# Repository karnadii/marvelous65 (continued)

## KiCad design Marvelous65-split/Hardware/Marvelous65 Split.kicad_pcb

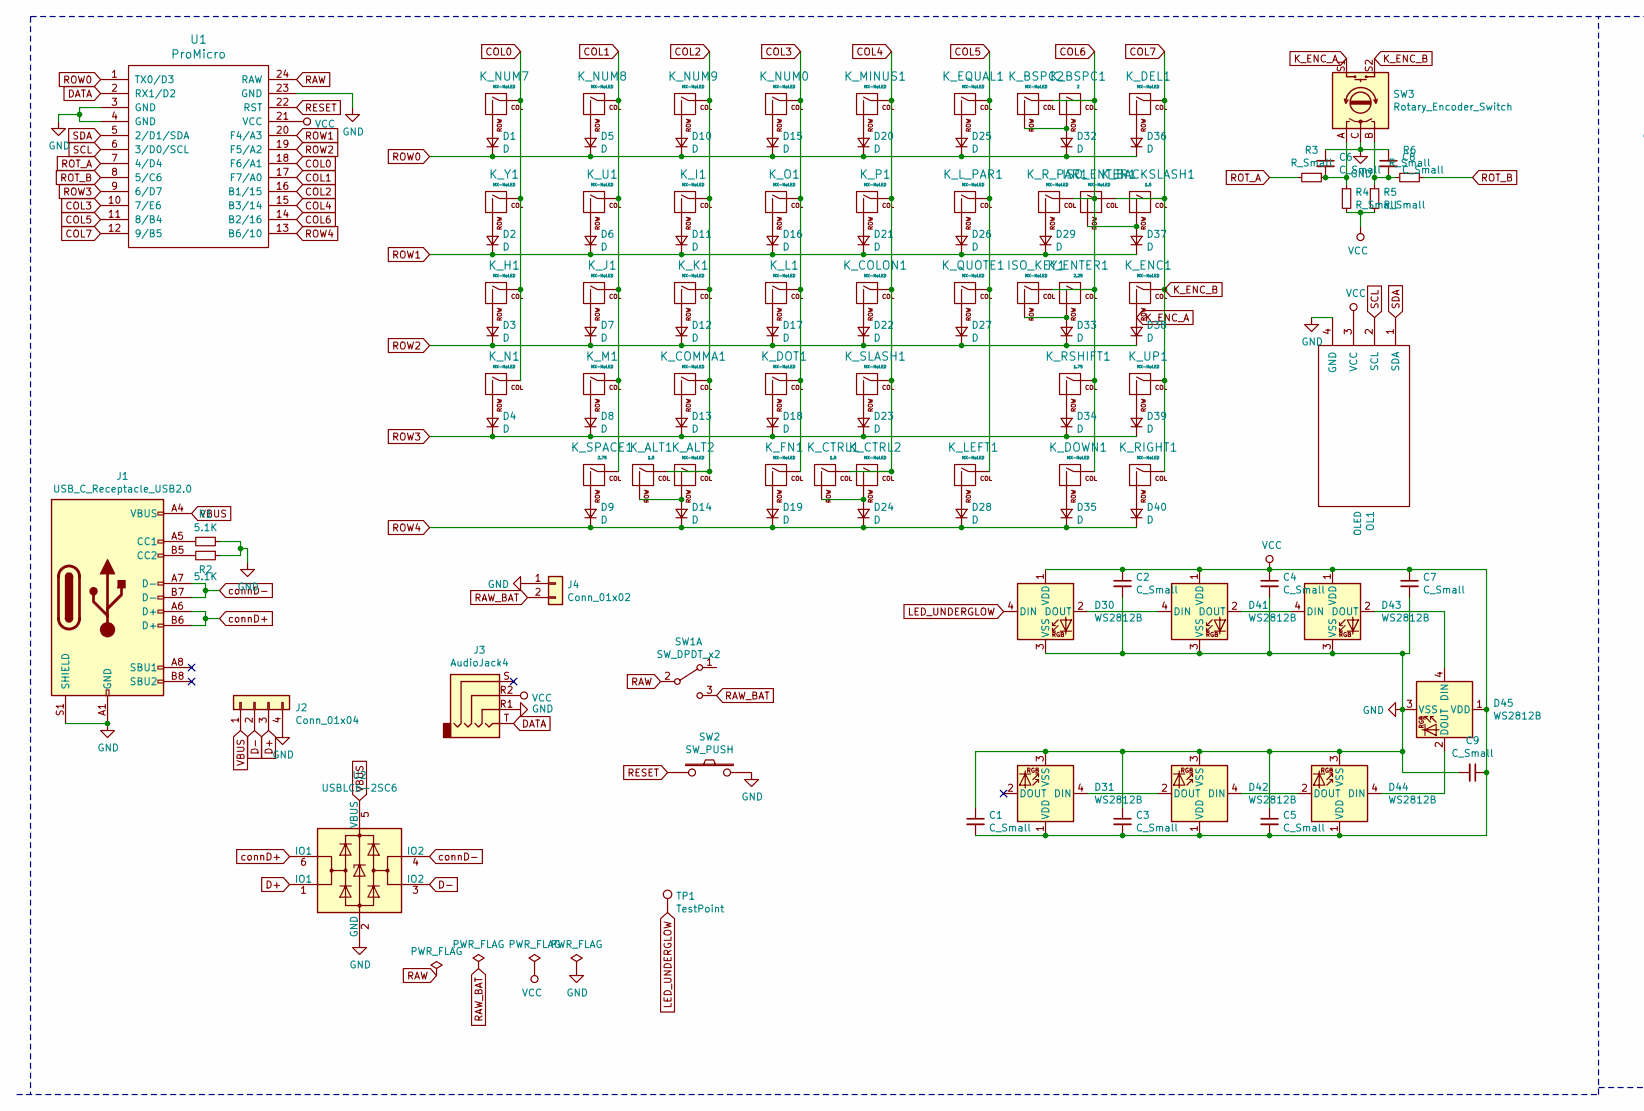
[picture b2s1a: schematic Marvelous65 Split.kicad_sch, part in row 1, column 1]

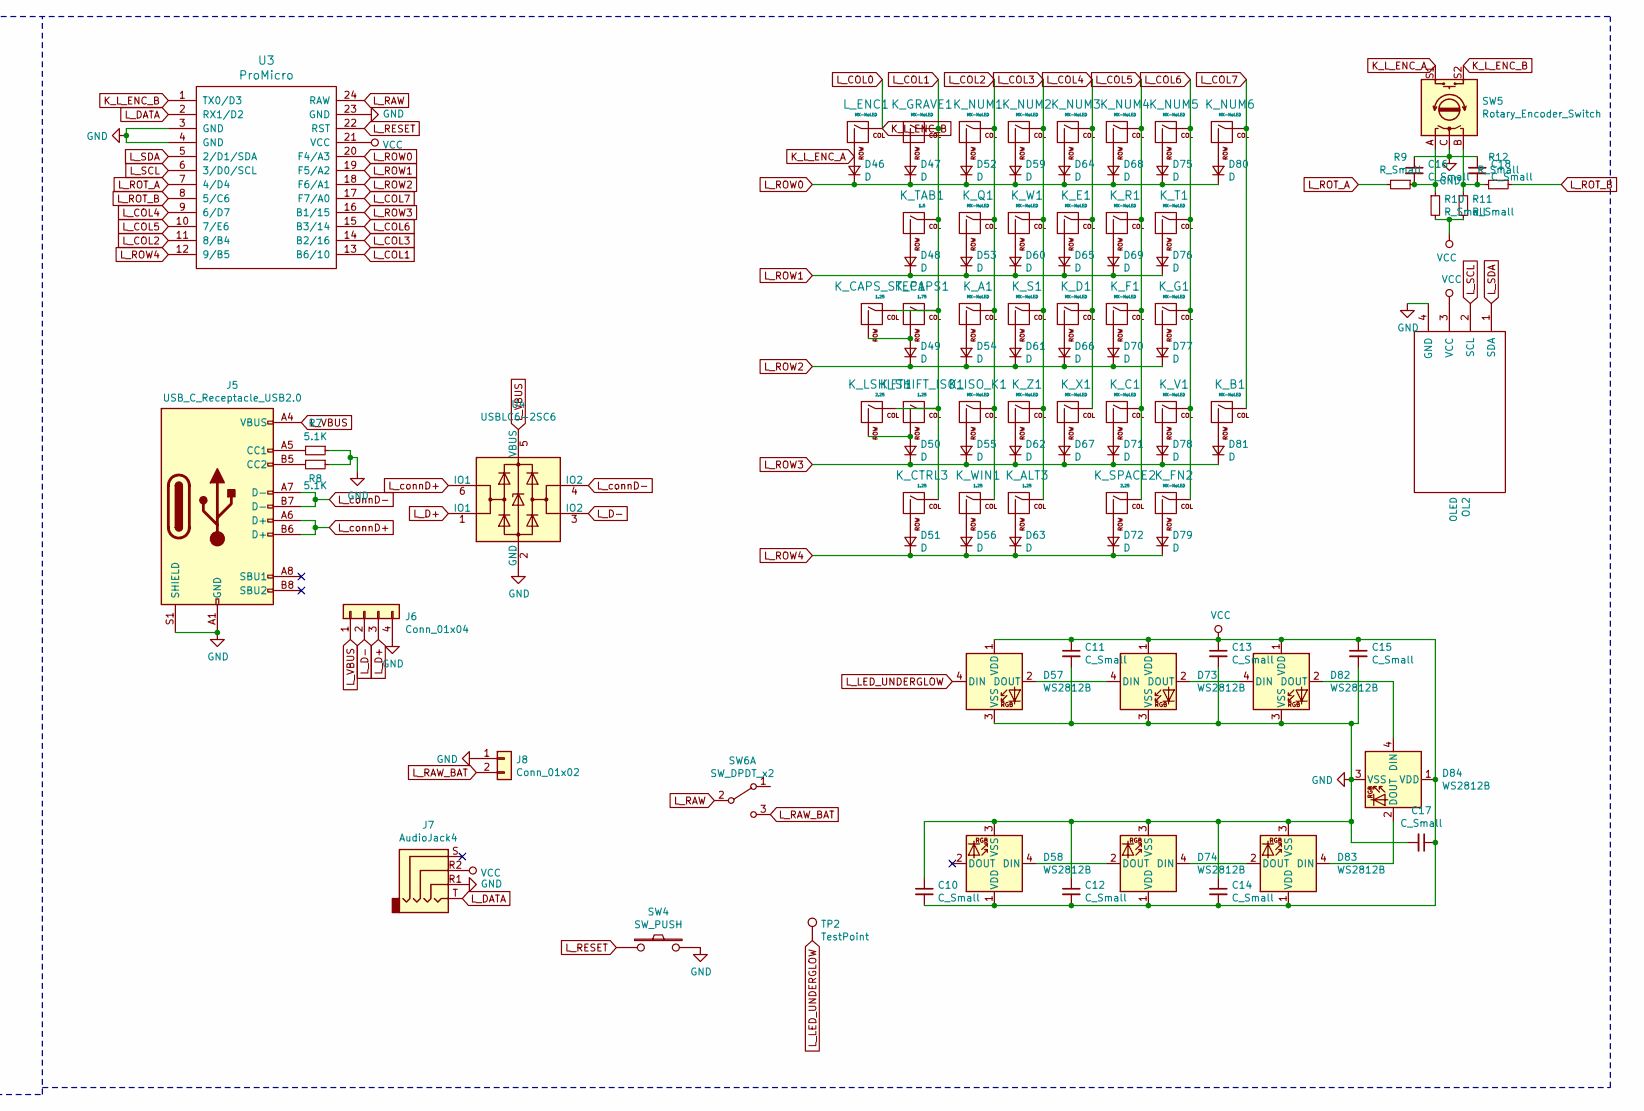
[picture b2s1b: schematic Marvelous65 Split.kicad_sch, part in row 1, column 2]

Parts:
C1, C2, C3, C4, C5, C6, C7, C8, C9, C10, C11, C12, C13, C14, C15, C16, C17, C18: C_Small; C_0805_2012Metric_Pad1.15x1.40mm_HandSolder
D1, D2, D3, D4, D5, D6, D7, D8, D9, D10, D11, D12, D13, D14, D15, D16, D17, D18, D19, D20, D21, D22, D23, D24, D25, D26, D27, D28, D29, D32, D33, D34, D35, D36, D37, D38, D39, D40, D46, D47, D48, D49, D50, D51, D52, D53, D54, D55, D56, D59, D60, D61, D62, D63, D64, D65, D66, D67, D68, D69, D70, D71, D72, D75, D76, D77, D78, D79, D80, D81: D; D_SOD-123
D30, D31, D41, D42, D43, D44, D45, D57, D58, D73, D74, D82, D83, D84: WS2812B; LED_WS2812B_PLCC4_5.0x5.0mm_P3.2mm
ISO_ENTER1: MX-NoLED; MXOnly-ISO-ROTATED-ReversedStabilizers-NoLED
ISO_KEY1: MX-NoLED; MXOnly-1U-NoLED
J1, J5: USB_C_Receptacle_USB2.0; USB_C_Receptacle_HRO_TYPE-C-31-M-12
J2, J6: Conn_01x04; PinSocket_1x04_P2.54mm_Vertical
J3, J7: AudioJack4; Jack_3.5mm_PJ320D_Horizontal
J4, J8: Conn_01x02; JST_XH_S2B-XH-A_1x02_P2.50mm_Horizontal
K_A1: MX-NoLED; MXOnly-1U-NoLED
K_ALT1: 1.5; MXOnly-1.5U-NoLED
K_ALT2: MX-NoLED; MXOnly-1U-NoLED
K_ALT3: 1.25; MXOnly-1.25U-NoLED
K_B1: MX-NoLED; MXOnly-1U-NoLED
K_BACKSLASH1: 1.5; MXOnly-1.5U-NoLED
K_BSPC1: 2; MXOnly-2U-NoLED
K_BSPC2: MX-NoLED; MXOnly-1U-NoLED
K_C1: MX-NoLED; MXOnly-1U-NoLED
K_CAPS1: 1.75; MXOnly-1.75U-NoLED
K_CAPS_STEP1: 1.25; MXOnly-1.25U-NoLED
K_COLON1: MX-NoLED; MXOnly-1U-NoLED
K_COMMA1: MX-NoLED; MXOnly-1U-NoLED
K_CTRL1: 1.5; MXOnly-1.5U-NoLED
K_CTRL2: MX-NoLED; MXOnly-1U-NoLED
K_CTRL3: 1.25; MXOnly-1.25U-NoLED
K_D1: MX-NoLED; MXOnly-1U-NoLED
K_DEL1: MX-NoLED; MXOnly-1U-NoLED
K_DOT1: MX-NoLED; MXOnly-1U-NoLED
K_DOWN1: MX-NoLED; MXOnly-1U-NoLED
K_E1: MX-NoLED; MXOnly-1U-NoLED
K_ENC1: MX-NoLED; MXOnly-1U-NoLED
K_ENTER1: 2.25; MXOnly-2.25U-NoLED
K_EQUAL1: MX-NoLED; MXOnly-1U-NoLED
K_F1: MX-NoLED; MXOnly-1U-NoLED
K_FN1: MX-NoLED; MXOnly-1U-NoLED
K_FN2: MX-NoLED; MXOnly-1.25U-NoLED
K_G1: MX-NoLED; MXOnly-1U-NoLED
K_GRAVE1: MX-NoLED; MXOnly-1U-NoLED
K_H1: MX-NoLED; MXOnly-1U-NoLED
K_I1: MX-NoLED; MXOnly-1U-NoLED
K_ISO_K1: MX-NoLED; MXOnly-1U-NoLED
K_J1: MX-NoLED; MXOnly-1U-NoLED
K_K1: MX-NoLED; MXOnly-1U-NoLED
K_L1: MX-NoLED; MXOnly-1U-NoLED
K_LEFT1: MX-NoLED; MXOnly-1U-NoLED
K_LSHIFT1: 2.25; MXOnly-2.25U-NoLED
K_L_PAR1: MX-NoLED; MXOnly-1U-NoLED
K_M1: MX-NoLED; MXOnly-1U-NoLED
K_MINUS1: MX-NoLED; MXOnly-1U-NoLED
K_N1: MX-NoLED; MXOnly-1U-NoLED
K_NUM0, K_NUM1, K_NUM2, K_NUM3, K_NUM4, K_NUM5, K_NUM6, K_NUM7, K_NUM8, K_NUM9: MX-NoLED; MXOnly-1U-NoLED
K_O1: MX-NoLED; MXOnly-1U-NoLED
K_P1: MX-NoLED; MXOnly-1U-NoLED
K_Q1: MX-NoLED; MXOnly-1U-NoLED
K_QUOTE1: MX-NoLED; MXOnly-1U-NoLED
K_R1: MX-NoLED; MXOnly-1U-NoLED
K_RIGHT1: MX-NoLED; MXOnly-1U-NoLED
K_RSHIFT1: 1.75; MXOnly-1.75U-NoLED
K_R_PAR1: MX-NoLED; MXOnly-1U-NoLED
K_S1: MX-NoLED; MXOnly-1U-NoLED
K_SHIFT_ISO1: 1.25; MXOnly-1.25U-NoLED
K_SLASH1: MX-NoLED; MXOnly-1U-NoLED
K_SPACE1: 2.75; MXOnly-2.75U-ReversedStabilizers-NoLED
K_SPACE2: 2.25; MXOnly-2.25U-ReversedStabilizers-NoLED
K_T1: MX-NoLED; MXOnly-1U-NoLED
K_TAB1: 1.5; MXOnly-1.5U-NoLED
K_U1: MX-NoLED; MXOnly-1U-NoLED
K_UP1: MX-NoLED; MXOnly-1U-NoLED
K_V1: MX-NoLED; MXOnly-1U-NoLED
K_W1: MX-NoLED; MXOnly-1U-NoLED
K_WIN1: 1.25; MXOnly-1.25U-NoLED
K_X1: MX-NoLED; MXOnly-1U-NoLED
K_Y1: MX-NoLED; MXOnly-1U-NoLED
K_Z1: MX-NoLED; MXOnly-1U-NoLED
L_ENC1: MX-NoLED; MXOnly-1U-NoLED
OL1, OL2: OLED
R1, R2, R7, R8: 5.1K; R_0603_1608Metric_Pad1.05x0.95mm_HandSolder
R3, R4, R5, R6, R9, R10, R11, R12: R_Small; R_0603_1608Metric_Pad1.05x0.95mm_HandSolder
SW1, SW6: SW_DPDT_x2; SW_SPDT_PCM12
SW2, SW4: SW_PUSH; SW_SPST_TL3342
SW3, SW5: Rotary_Encoder_Switch; RotaryEncoder_Alps_EC11E-Switch_Vertical_H20mm
TP1, TP2: TestPoint; TestPoint_THTPad_D2.5mm_Drill1.2mm
U1, U3: ProMicro; ProMicro_v3
U2, U4: USBLC6-2SC6; SOT-23-6

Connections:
COL0: K_H1.1 (COL), K_N1.1 (COL), K_NUM7.1 (COL), K_Y1.1 (COL), U1.18 (F6/A1)
COL1: K_J1.1 (COL), K_M1.1 (COL), K_NUM8.1 (COL), K_SPACE1.1 (COL), K_U1.1 (COL), U1.17 (F7/A0)
COL2: K_ALT1.1 (COL), K_ALT2.1 (COL), K_COMMA1.1 (COL), K_I1.1 (COL), K_K1.1 (COL), K_NUM9.1 (COL), U1.16 (B1/15)
COL3: K_DOT1.1 (COL), K_FN1.1 (COL), K_L1.1 (COL), K_NUM0.1 (COL), K_O1.1 (COL), U1.10 (7/E6)
COL4: K_COLON1.1 (COL), K_CTRL1.1 (COL), K_CTRL2.1 (COL), K_MINUS1.1 (COL), K_P1.1 (COL), K_SLASH1.1 (COL), U1.15 (B3/14)
COL5: K_EQUAL1.1 (COL), K_LEFT1.1 (COL), K_L_PAR1.1 (COL), K_QUOTE1.1 (COL), U1.11 (8/B4)
COL6: ISO_KEY1.1 (COL), K_BSPC1.1 (COL), K_BSPC2.1 (COL), K_DOWN1.1 (COL), K_ENTER1.1 (COL), K_RSHIFT1.1 (COL), K_R_PAR1.1 (COL), U1.14 (B2/16)
COL7: ISO_ENTER1.1 (COL), K_BACKSLASH1.1 (COL), K_DEL1.1 (COL), K_ENC1.1 (COL), K_RIGHT1.1 (COL), K_UP1.1 (COL), SW3.S2, U1.12 (9/B5)
D+: J2.3, U2.1 (IO1)
D-: J2.2, U2.3 (IO2)
DATA: J3.T, U1.2 (RX1/D2)
GND: C1.1, C2.2, C3.1, C4.2, C5.1, C6.1, C7.2, C8.1, C9.2, C10.1, C11.2, C12.1, C13.2, C14.1, C15.2, C16.1, C17.2, C18.1, D30.3 (VSS), D31.3 (VSS), D41.3 (VSS), D42.3 (VSS), D43.3 (VSS), D44.3 (VSS), D45.3 (VSS), D57.3 (VSS), D58.3 (VSS), D73.3 (VSS), D74.3 (VSS), D82.3 (VSS), D83.3 (VSS), D84.3 (VSS), J1.A1 (GND), J1.A12 (GND), J1.B1 (GND), J1.B12 (GND), J1.S1 (SHIELD), J2.4, J3.R1, J4.1, J5.A1 (GND), J5.A12 (GND), J5.B1 (GND), J5.B12 (GND), J5.S1 (SHIELD), J6.4, J7.R1, J8.1, OL1.4 (GND), OL2.4 (GND), R1.1, R2.1, R7.1, R8.1, SW2.2, SW3.C, SW4.2, SW5.C, U1.3 (GND), U1.4 (GND), U1.23 (GND), U2.2 (GND), U3.3 (GND), U3.4 (GND), U3.23 (GND), U4.2 (GND)
K_ENC_A: D38.2 (A), K_ENC1.2 (ROW), SW3.S1
K_L_ENC_A: D46.2 (A), L_ENC1.2 (ROW), SW5.S1
K_L_ENC_B: L_ENC1.1 (COL), SW5.S2, U3.1 (TX0/D3)
LED_UNDERGLOW: D30.4 (DIN), TP1.1
L_COL1: K_CAPS1.1 (COL), K_CAPS_STEP1.1 (COL), K_CTRL3.1 (COL), K_GRAVE1.1 (COL), K_LSHIFT1.1 (COL), K_SHIFT_ISO1.1 (COL), K_TAB1.1 (COL), U3.13 (B6/10)
L_COL2: K_A1.1 (COL), K_ISO_K1.1 (COL), K_NUM1.1 (COL), K_Q1.1 (COL), K_WIN1.1 (COL), U3.11 (8/B4)
L_COL3: K_ALT3.1 (COL), K_NUM2.1 (COL), K_S1.1 (COL), K_W1.1 (COL), K_Z1.1 (COL), U3.14 (B2/16)
L_COL4: K_D1.1 (COL), K_E1.1 (COL), K_NUM3.1 (COL), K_X1.1 (COL), U3.9 (6/D7)
L_COL5: K_C1.1 (COL), K_F1.1 (COL), K_NUM4.1 (COL), K_R1.1 (COL), K_SPACE2.1 (COL), U3.10 (7/E6)
L_COL6: K_FN2.1 (COL), K_G1.1 (COL), K_NUM5.1 (COL), K_T1.1 (COL), K_V1.1 (COL), U3.15 (B3/14)
L_COL7: K_B1.1 (COL), K_NUM6.1 (COL), U3.17 (F7/A0)
L_D+: J6.3, U4.1 (IO1)
L_D-: J6.2, U4.3 (IO2)
L_DATA: J7.T, U3.2 (RX1/D2)
L_LED_UNDERGLOW: D57.4 (DIN), TP2.1
L_RAW: SW6.2 (B), U3.24 (RAW)
L_RAW_BAT: J8.2, SW6.3 (C)
L_RESET: SW4.1, U3.22 (RST)
L_ROTA_A: C16.2, R9.1, R10.1, SW5.A; also elsewhere on the board
L_ROTA_B: C18.2, R11.1, R12.2, SW5.B; also elsewhere on the board
L_ROT_A: R9.2, U3.7 (4/D4); also elsewhere on the board
L_ROT_B: R12.1, U3.8 (5/C6); also elsewhere on the board
L_ROW0: D46.1 (K), D47.1 (K), D52.1 (K), D59.1 (K), D64.1 (K), D68.1 (K), D75.1 (K), D80.1 (K), U3.20 (F4/A3)
L_ROW1: D48.1 (K), D53.1 (K), D60.1 (K), D65.1 (K), D69.1 (K), D76.1 (K), U3.19 (F5/A2)
L_ROW2: D49.1 (K), D54.1 (K), D61.1 (K), D66.1 (K), D70.1 (K), D77.1 (K), U3.18 (F6/A1)
L_ROW3: D50.1 (K), D55.1 (K), D62.1 (K), D67.1 (K), D71.1 (K), D78.1 (K), D81.1 (K), U3.16 (B1/15)
L_ROW4: D51.1 (K), D56.1 (K), D63.1 (K), D72.1 (K), D79.1 (K), U3.12 (9/B5)
L_SCL: OL2.2 (SCL), U3.6 (3/D0/SCL)
L_SDA: OL2.1 (SDA), U3.5 (2/D1/SDA)
L_VBUS: J5.A4 (VBUS), J5.A9 (VBUS), J5.B4 (VBUS), J5.B9 (VBUS), J6.1, U4.5 (VBUS)
L_connD+: J5.A6 (D+), J5.B6 (D+), U4.6 (IO1)
L_connD-: J5.A7 (D-), J5.B7 (D-), U4.4 (IO2)
unnamed: D1.2 (A), K_NUM7.2 (ROW)
unnamed: D2.2 (A), K_Y1.2 (ROW)
unnamed: D3.2 (A), K_H1.2 (ROW)
unnamed: D4.2 (A), K_N1.2 (ROW)
unnamed: D5.2 (A), K_NUM8.2 (ROW)
unnamed: D6.2 (A), K_U1.2 (ROW)
unnamed: D7.2 (A), K_J1.2 (ROW)
unnamed: D8.2 (A), K_M1.2 (ROW)
unnamed: D9.2 (A), K_SPACE1.2 (ROW)
unnamed: D10.2 (A), K_NUM9.2 (ROW)
unnamed: D11.2 (A), K_I1.2 (ROW)
unnamed: D12.2 (A), K_K1.2 (ROW)
unnamed: D13.2 (A), K_COMMA1.2 (ROW)
unnamed: D14.2 (A), K_ALT1.2 (ROW), K_ALT2.2 (ROW)
unnamed: D15.2 (A), K_NUM0.2 (ROW)
unnamed: D16.2 (A), K_O1.2 (ROW)
unnamed: D17.2 (A), K_L1.2 (ROW)
unnamed: D18.2 (A), K_DOT1.2 (ROW)
unnamed: D19.2 (A), K_FN1.2 (ROW)
unnamed: D20.2 (A), K_MINUS1.2 (ROW)
unnamed: D21.2 (A), K_P1.2 (ROW)
unnamed: D22.2 (A), K_COLON1.2 (ROW)
unnamed: D23.2 (A), K_SLASH1.2 (ROW)
unnamed: D24.2 (A), K_CTRL1.2 (ROW), K_CTRL2.2 (ROW)
unnamed: D25.2 (A), K_EQUAL1.2 (ROW)
unnamed: D26.2 (A), K_L_PAR1.2 (ROW)
unnamed: D27.2 (A), K_QUOTE1.2 (ROW)
unnamed: D28.2 (A), K_LEFT1.2 (ROW)
unnamed: D29.2 (A), K_R_PAR1.2 (ROW)
unnamed: D30.2 (DOUT), D41.4 (DIN)
unnamed: D31.4 (DIN), D42.2 (DOUT)
unnamed: D32.2 (A), K_BSPC1.2 (ROW), K_BSPC2.2 (ROW)
unnamed: D33.2 (A), ISO_KEY1.2 (ROW), K_ENTER1.2 (ROW)
unnamed: D34.2 (A), K_RSHIFT1.2 (ROW)
unnamed: D35.2 (A), K_DOWN1.2 (ROW)
unnamed: D36.2 (A), K_DEL1.2 (ROW)
unnamed: D37.2 (A), ISO_ENTER1.2 (ROW), K_BACKSLASH1.2 (ROW)
unnamed: D39.2 (A), K_UP1.2 (ROW)
unnamed: D40.2 (A), K_RIGHT1.2 (ROW)
unnamed: D41.2 (DOUT), D43.4 (DIN)
unnamed: D42.4 (DIN), D44.2 (DOUT)
unnamed: D43.2 (DOUT), D45.4 (DIN)
unnamed: D44.4 (DIN), D45.2 (DOUT)
unnamed: D47.2 (A), K_GRAVE1.2 (ROW)
unnamed: D48.2 (A), K_TAB1.2 (ROW)
unnamed: D49.2 (A), K_CAPS1.2 (ROW), K_CAPS_STEP1.2 (ROW)
unnamed: D50.2 (A), K_LSHIFT1.2 (ROW), K_SHIFT_ISO1.2 (ROW)
unnamed: D51.2 (A), K_CTRL3.2 (ROW)
unnamed: D52.2 (A), K_NUM1.2 (ROW)
unnamed: D53.2 (A), K_Q1.2 (ROW)
unnamed: D54.2 (A), K_A1.2 (ROW)
unnamed: D55.2 (A), K_ISO_K1.2 (ROW)
unnamed: D56.2 (A), K_WIN1.2 (ROW)
unnamed: D57.2 (DOUT), D73.4 (DIN)
unnamed: D58.4 (DIN), D74.2 (DOUT)
unnamed: D59.2 (A), K_NUM2.2 (ROW)
unnamed: D60.2 (A), K_W1.2 (ROW)
unnamed: D61.2 (A), K_S1.2 (ROW)
unnamed: D62.2 (A), K_Z1.2 (ROW)
unnamed: D63.2 (A), K_ALT3.2 (ROW)
unnamed: D64.2 (A), K_NUM3.2 (ROW)
unnamed: D65.2 (A), K_E1.2 (ROW)
unnamed: D66.2 (A), K_D1.2 (ROW)
unnamed: D67.2 (A), K_X1.2 (ROW)
unnamed: D68.2 (A), K_NUM4.2 (ROW)
unnamed: D69.2 (A), K_R1.2 (ROW)
unnamed: D70.2 (A), K_F1.2 (ROW)
unnamed: D71.2 (A), K_C1.2 (ROW)
unnamed: D72.2 (A), K_SPACE2.2 (ROW)
unnamed: D73.2 (DOUT), D82.4 (DIN)
unnamed: D74.4 (DIN), D83.2 (DOUT)
unnamed: D75.2 (A), K_NUM5.2 (ROW)
unnamed: D76.2 (A), K_T1.2 (ROW)
unnamed: D77.2 (A), K_G1.2 (ROW)
unnamed: D78.2 (A), K_V1.2 (ROW)
unnamed: D79.2 (A), K_FN2.2 (ROW)
unnamed: D80.2 (A), K_NUM6.2 (ROW)
unnamed: D81.2 (A), K_B1.2 (ROW)
unnamed: D82.2 (DOUT), D84.4 (DIN)
unnamed: D83.4 (DIN), D84.2 (DOUT)
unnamed: J1.A5 (CC1), R1.2
unnamed: J1.B5 (CC2), R2.2
unnamed: J5.A5 (CC1), R7.2
unnamed: J5.B5 (CC2), R8.2
RAW: SW1.2 (B), U1.24 (RAW)
RAW_BAT: J4.2, SW1.3 (C)
RESET: SW2.1, U1.22 (RST)
ROTA_A: C6.2, R3.1, R4.1, SW3.A; also elsewhere on the board
ROTA_B: C8.2, R5.1, R6.2, SW3.B; also elsewhere on the board
ROT_A: R3.2, U1.7 (4/D4); also elsewhere on the board
ROT_B: R6.1, U1.8 (5/C6); also elsewhere on the board
ROW0: D1.1 (K), D5.1 (K), D10.1 (K), D15.1 (K), D20.1 (K), D25.1 (K), D32.1 (K), D36.1 (K), U1.1 (TX0/D3)
ROW1: D2.1 (K), D6.1 (K), D11.1 (K), D16.1 (K), D21.1 (K), D26.1 (K), D29.1 (K), D37.1 (K), U1.20 (F4/A3)
ROW2: D3.1 (K), D7.1 (K), D12.1 (K), D17.1 (K), D22.1 (K), D27.1 (K), D33.1 (K), D38.1 (K), U1.19 (F5/A2)
ROW3: D4.1 (K), D8.1 (K), D13.1 (K), D18.1 (K), D23.1 (K), D34.1 (K), D39.1 (K), U1.9 (6/D7)
ROW4: D9.1 (K), D14.1 (K), D19.1 (K), D24.1 (K), D28.1 (K), D35.1 (K), D40.1 (K), U1.13 (B6/10)
SCL: OL1.2 (SCL), U1.6 (3/D0/SCL)
SDA: OL1.1 (SDA), U1.5 (2/D1/SDA)
VBUS: J1.A4 (VBUS), J1.A9 (VBUS), J1.B4 (VBUS), J1.B9 (VBUS), J2.1, U2.5 (VBUS)
VCC: C1.2, C2.1, C3.2, C4.1, C5.2, C7.1, C9.1, C10.2, C11.1, C12.2, C13.1, C14.2, C15.1, C17.1, D30.1 (VDD), D31.1 (VDD), D41.1 (VDD), D42.1 (VDD), D43.1 (VDD), D44.1 (VDD), D45.1 (VDD), D57.1 (VDD), D58.1 (VDD), D73.1 (VDD), D74.1 (VDD), D82.1 (VDD), D83.1 (VDD), D84.1 (VDD), J3.R2, J7.R2, OL1.3 (VCC), OL2.3 (VCC), R4.2, R5.2, R10.2, R11.2, U1.21 (VCC), U3.21 (VCC)
connD+: J1.A6 (D+), J1.B6 (D+), U2.6 (IO1)
connD-: J1.A7 (D-), J1.B7 (D-), U2.4 (IO2)

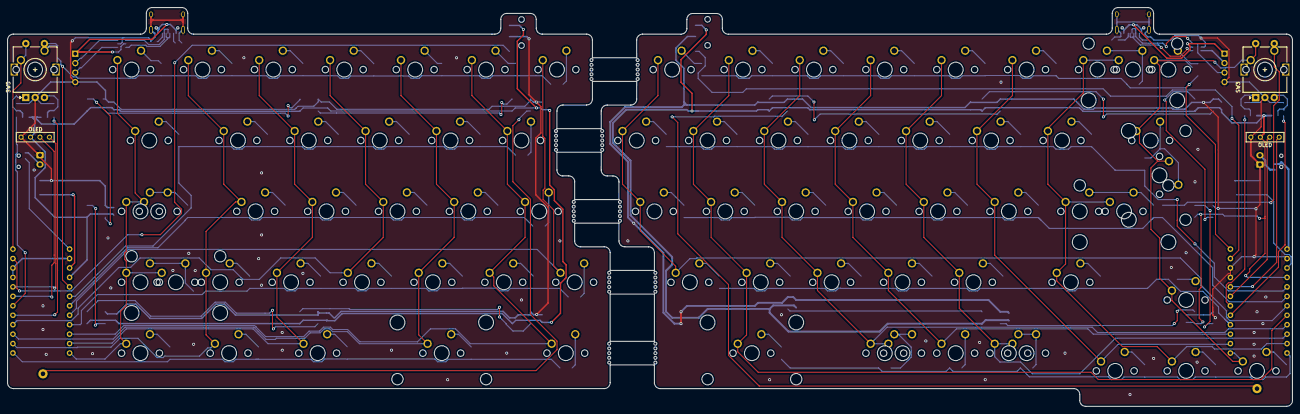
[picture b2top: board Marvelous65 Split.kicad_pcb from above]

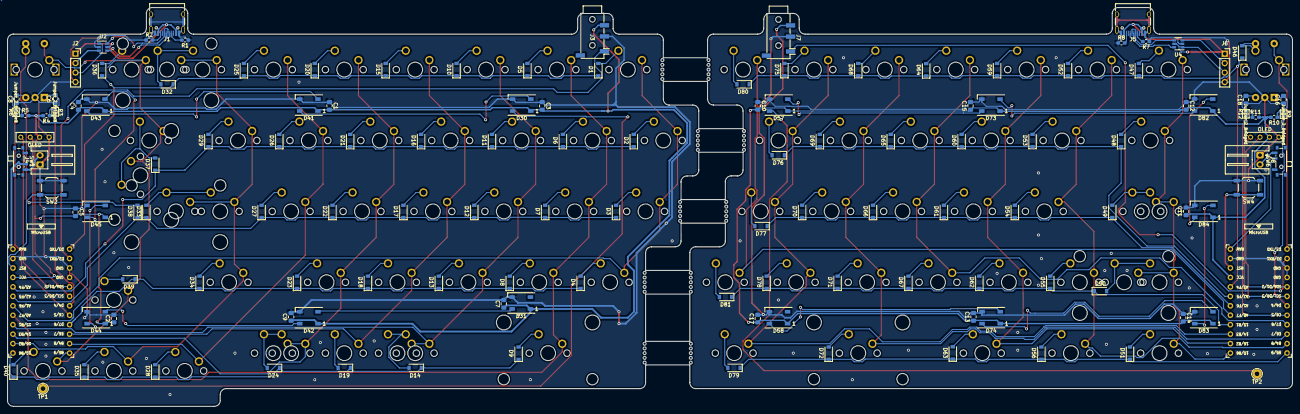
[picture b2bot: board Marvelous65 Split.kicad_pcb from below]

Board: 2 copper layers, 345.3 x 107.2 mm, 217 parts (137 on the bottom side), 146 nets.

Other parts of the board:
JP1, JP2, JP3, JP4: Jumper_2_Bridged; Jumper

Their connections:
L_ROTA_A: JP3.2; also elsewhere on the board
L_ROTA_B: JP4.2; also elsewhere on the board
L_ROT_A: JP3.1; also elsewhere on the board
L_ROT_B: JP4.1; also elsewhere on the board
ROTA_A: JP2.1; also elsewhere on the board
ROTA_B: JP1.1; also elsewhere on the board
ROT_A: JP2.2; also elsewhere on the board
ROT_B: JP1.2; also elsewhere on the board

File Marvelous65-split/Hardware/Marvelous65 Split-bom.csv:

Comment,Designator,Footprint,LCSC
"0.1uF","C1,C2,C3,C4,C5,C6,C7,C8,C9,C10,C11,C12,C13,C14,C15,C16,C17,C18","Capacitor_SMD:C_0805_2012Metric_Pad1.15x1.40mm_HandSolder","C49678"
"D","D1,D2,D3,D4,D5,D6,D7,D8,D9,D10,D11,D12,D13,D14,D15,D16,D17,D18,D19,D20,D21,D22,D23,D24,D25,D26,D27,D28,D29,D32,D33,D34,D35,D36,D37,D38,D39,D40,D46,D47,D48,D49,D50,D51,D52,D53,D54,D55,D56,D59,D60,D61,D62,D63,D64,D65,D66,D67,D68,D69,D70,D71,D72,D75,D76,D77,D78,D79,D80,D81","Diode_SMD:D_SOD-123","C81598"
"WS2812B","D30,D31,D41,D42,D43,D44,D45,D57,D58,D73,D74,D82,D83,D84","LED_SMD:LED_WS2812B_PLCC4_5.0x5.0mm_P3.2mm",""
"MX-NoLED","ISO_ENTER1","MX_Only:MXOnly-ISO-ROTATED-ReversedStabilizers-NoLED",""
"USB_C_Receptacle_USB2.0","J1,J5","Connector_USB:USB_C_Receptacle_HRO_TYPE-C-31-M-12","C165948"
"Conn_01x04","J2,J6","Connector_PinSocket_2.54mm:PinSocket_1x04_P2.54mm_Vertical",""
"AudioJack4","J3,J7","Connector_Audio:Jack_3.5mm_PJ320D_Horizontal","C15139"
"Conn_01x02","J4,J8","Connector_JST:JST_XH_S2B-XH-A_1x02_P2.50mm_Horizontal","C157931"
"Jumper_2_Bridged","JP1,JP2,JP3,JP4","SofleKeyboard-footprint:Jumper",""
"1.5","K_BACKSLASH1,K_CTRL1,K_ALT1,K_TAB1","MX_Only:MXOnly-1.5U-NoLED",""
"2","K_BSPC1","MX_Only:MXOnly-2U-NoLED",""
"2.25","K_ENTER1,K_LSHIFT1","MX_Only:MXOnly-2.25U-NoLED",""
"MX-NoLED","K_FN2","MX_Only:MXOnly-1.25U-NoLED",""
"MX-NoLED","K_NUM0,K_MINUS1,K_EQUAL1,K_O1,K_P1,K_L_PAR1,K_R_PAR1,K_ENC1,K_DEL1,K_I1,K_U1,K_Y1,K_H1,K_J1,K_K1,K_L1,K_DOT1,K_SLASH1,K_UP1,K_QUOTE1,K_COLON1,K_COMMA1,K_M1,K_N1,K_FN1,K_RIGHT1,K_DOWN1,K_LEFT1,ISO_KEY1,L_ENC1,K_GRAVE1,K_NUM1,K_Q1,K_W1,K_E1,K_R1,K_T1,K_A1,K_S1,K_D1,K_F1,K_G1,K_ISO_K1,K_Z1,K_X1,K_C1,K_V1,K_B1,K_ALT2,K_CTRL2,K_BSPC2,K_NUM2,K_NUM3,K_NUM4,K_NUM5,K_NUM6,K_NUM7,K_NUM8,K_NUM9","MX_Only:MXOnly-1U-NoLED",""
"1.75","K_RSHIFT1,K_CAPS1","MX_Only:MXOnly-1.75U-NoLED",""
"1.25","K_SHIFT_ISO1,K_WIN1,K_CAPS_STEP1,K_CTRL3,K_ALT3","MX_Only:MXOnly-1.25U-NoLED",""
"2.75","K_SPACE1","MX_Only:MXOnly-2.75U-ReversedStabilizers-NoLED",""
"2.25","K_SPACE2","MX_Only:MXOnly-2.25U-ReversedStabilizers-NoLED",""
"OLED","OL1,OL2","kbd:OLED",""
"5.1K","R1,R2,R7,R8","Resistor_SMD:R_0603_1608Metric_Pad1.05x0.95mm_HandSolder","C23186"
"10k","R3,R4,R5,R6,R9,R10,R11,R12","Resistor_SMD:R_0603_1608Metric_Pad1.05x0.95mm_HandSolder","C25804"
"SW_DPDT_x2","SW1,SW6","Button_Switch_SMD:SW_SPDT_PCM12","C221841"
"SW_PUSH","SW2,SW4","Button_Switch_SMD:SW_SPST_TL3342","C318884"
"Rotary_Encoder_Switch","SW3,SW5","Rotary_Encoder:RotaryEncoder_Alps_EC11E-Switch_Vertical_H20mm","C470748"
"TestPoint","TP1,TP2","TestPoint:TestPoint_THTPad_D2.5mm_Drill1.2mm",""
"ProMicro","U1,U3","kbd:ProMicro_v3",""
"USBLC6-2SC6","U2,U4","Package_TO_SOT_SMD:SOT-23-6","C558442"

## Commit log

2021-01-22 add case design
2021-01-22 add plate
2021-01-22 add dust cover design
2021-05-05 add PCB and other files
2021-05-07 add firmware
2021-05-07 Add BOM file for JLC
    add BOM file for fabrication
2021-05-07 add support link
2021-05-07 update TODO
2021-05-28 add IBOM
2021-05-28 fix folder name typo
2021-05-28 add battery image
